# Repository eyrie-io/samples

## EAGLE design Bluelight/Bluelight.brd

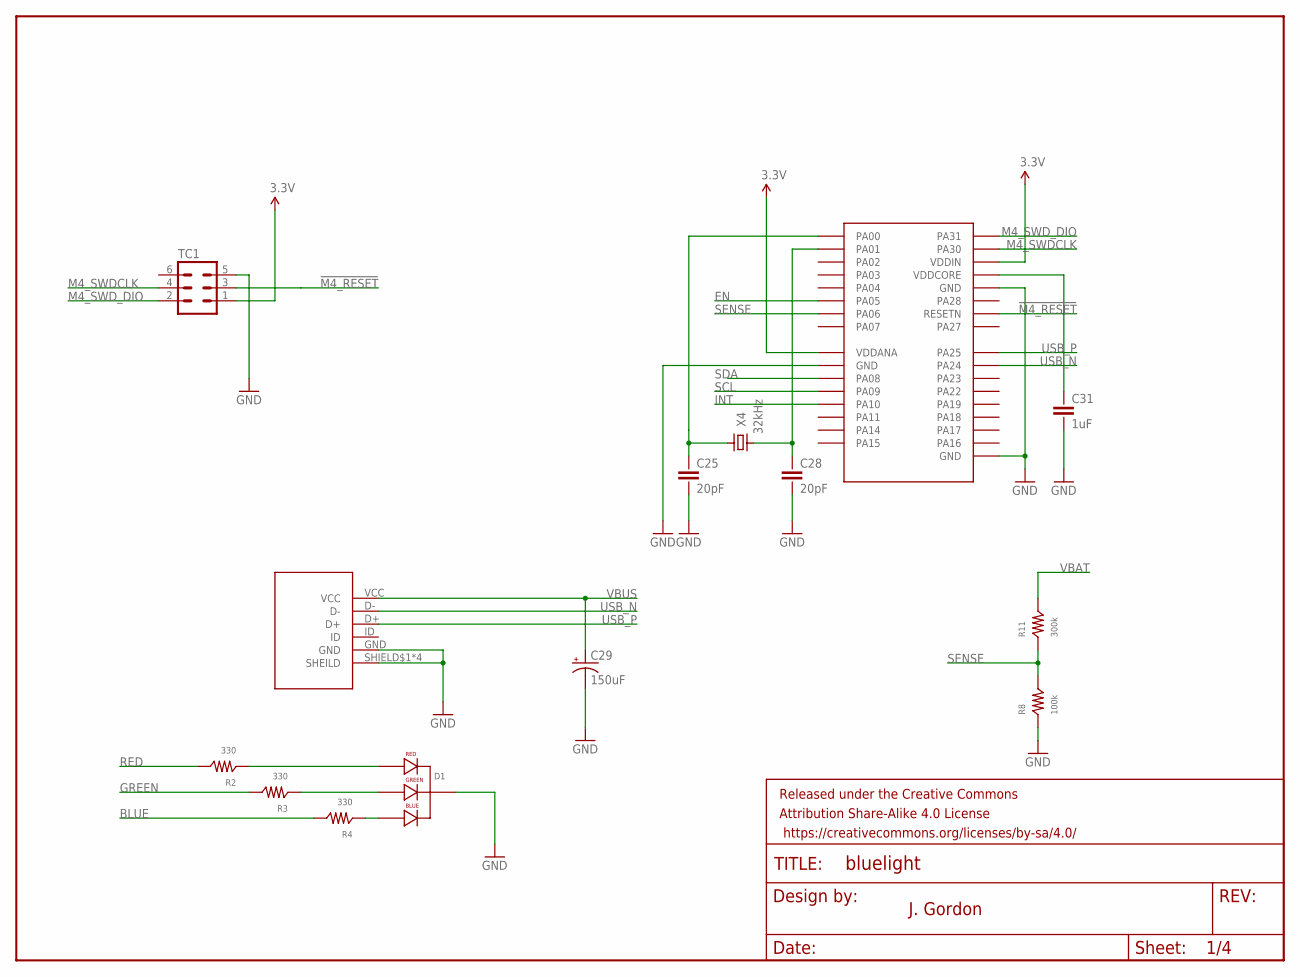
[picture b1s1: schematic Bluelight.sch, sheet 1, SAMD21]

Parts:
C25, C28: 20pF; CAP-0402
C29: 150uF; PANASONIC_C
C31: 1uF; CAP-0402
D1: LED-RGB-CC-THRUDIFFUSE; LED-RGB-THRU
FRAME3: FRAME-LETTERNO_PACKAGE; DUMMY
J5: 10118193-0001LF
R2, R3, R4: 330; RES-0402
R8: 100k; RES-0402
R11: 300k; RES-0402
TC1: TC2030-IDC-NL
U2: ATSAMD21E18A-MUT; QFN32
X4: 32kHz; CRYSTAL-3215

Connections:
3.3V: TC1.1, U2.9 (VDDANA), U2.30 (VDDIN); also elsewhere on the board
!M4_RESET: TC1.3, U2.26 (RESETN); also elsewhere on the board
BLUE: R4.2; also elsewhere on the board
EN: U2.6 (PA05); also elsewhere on the board
GND: C25.1 (2), C28.1 (2), C29.-, C31.1 (2), D1.2 (CATHODE), J5.GND, J5.SHIELD$1 (SHEILD), J5.SHIELD$2 (SHEILD), J5.SHIELD$3 (SHEILD), J5.SHIELD$4 (SHEILD), R8.1, TC1.5, U2.10 (GND), U2.28 (GND), U2.GND; also elsewhere on the board
GREEN: R3.2; also elsewhere on the board
INT: U2.13 (PA10); also elsewhere on the board
M4_SWDCLK: TC1.4, U2.31 (PA30)
M4_SWD_DIO: TC1.2, U2.32 (PA31)
unnamed: D1.4 (BLUE_CATHODE), R4.1
unnamed: D1.3 (GREEN_CATHODE), R3.1
unnamed: C28.2 (1), U2.2 (PA01), X4.P$1 (1)
unnamed: D1.1 (RED_CATHODE), R2.1
unnamed: C25.2 (1), U2.1 (PA00), X4.P$2 (3)
unnamed: C31.2 (1), U2.29 (VDDCORE)
RED: R2.2; also elsewhere on the board
SCL: U2.12 (PA09); also elsewhere on the board
SDA: U2.11 (PA08); also elsewhere on the board
SENSE: R8.2, R11.1, U2.7 (PA06)
USB_N: J5.D-, U2.23 (PA24)
USB_P: J5.D+, U2.24 (PA25)
VBAT: R11.2; also elsewhere on the board
VBUS: C29.+, J5.VCC; also elsewhere on the board

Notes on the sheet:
J. Gordon

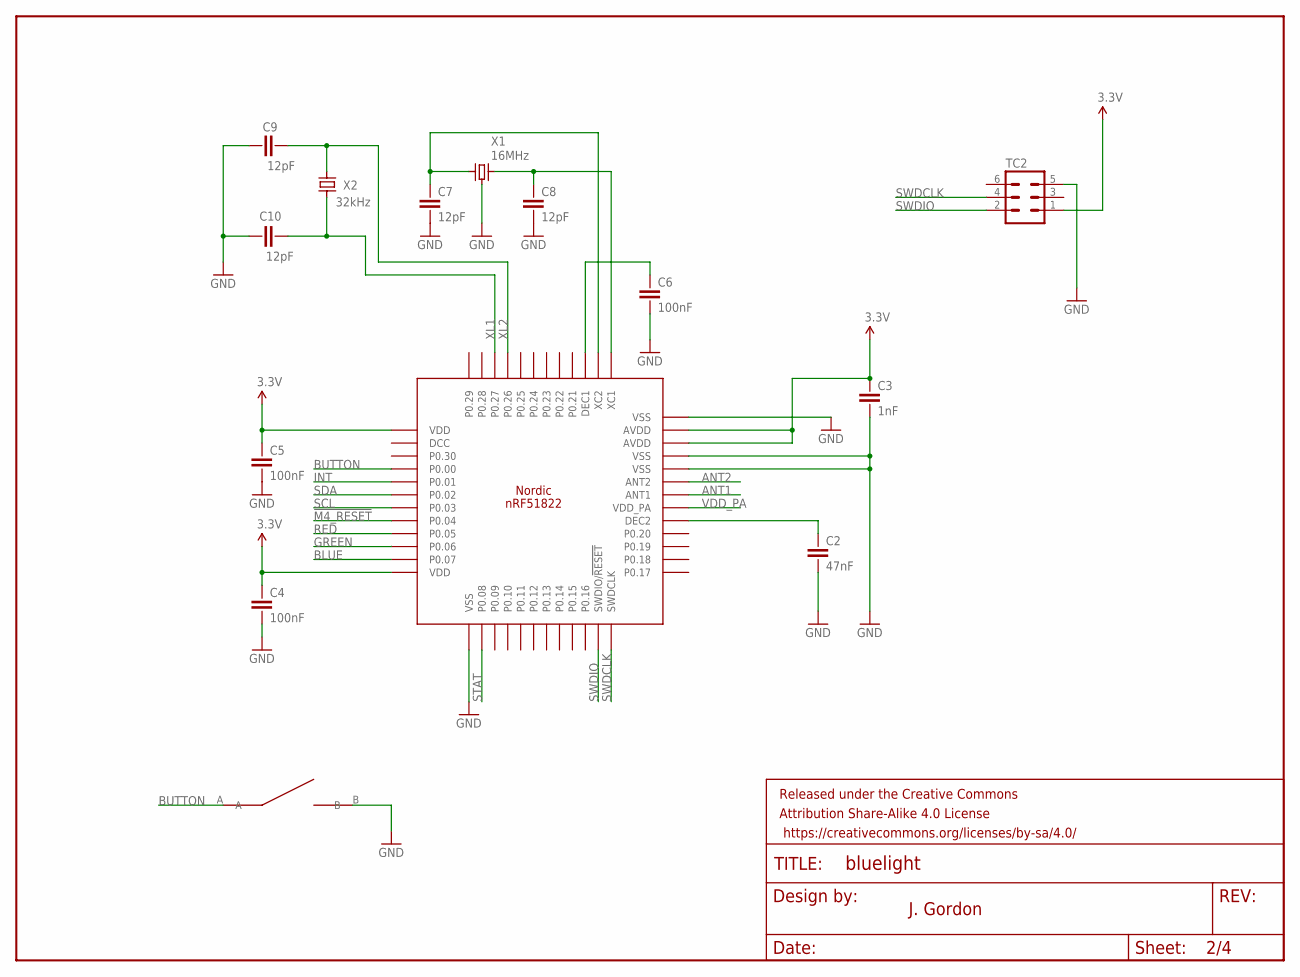
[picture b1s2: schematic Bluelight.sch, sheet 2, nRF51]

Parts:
C2: 47nF; CAP-0402
C3: 1nF; CAP-0402
C4, C5, C6: 100nF; CAP-0402
C7, C8, C9, C10: 12pF; CAP-0402
FRAME1: FRAME-LETTERNO_PACKAGE; DUMMY
TC2: TC2030-IDC-NL
U1: NRF51822
U$1: EVQ-PF206K
X1: 16MHz; CRYSTAL-2520
X2: 32kHz; CRYSTAL-3215

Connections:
3.3V: C3.2 (1), C4.2 (1), C5.2 (1), TC2.1, U1.AVDD@1 (AVDD), U1.AVDD@2 (AVDD), U1.VDD@1 (VDD), U1.VDD@2 (VDD); also elsewhere on the board
!M4_RESET: U1.P0.04; also elsewhere on the board
ANT1: U1.ANT1; also elsewhere on the board
ANT2: U1.ANT2; also elsewhere on the board
BLUE: U1.P0.07; also elsewhere on the board
BUTTON: U1.P0.00, U$1.A
GND: C2.1 (2), C3.1 (2), C4.1 (2), C5.1 (2), C6.1 (2), C7.1 (2), C8.1 (2), C9.2 (1), C10.2 (1), TC2.5, U1.VSS@1 (VSS), U1.VSS@2 (VSS), U1.VSS@3 (VSS), U1.VSS@4 (VSS), U$1.B, X1.GND@1 (GND), X1.GND@2 (GND); also elsewhere on the board
GREEN: U1.P0.06; also elsewhere on the board
INT: U1.P0.01; also elsewhere on the board
unnamed: C2.2 (1), U1.DEC2
unnamed: C6.2 (1), U1.DEC1
unnamed: C8.2 (1), U1.XC1, X1.3
unnamed: C7.2 (1), U1.XC2, X1.1
RED: U1.P0.05; also elsewhere on the board
SCL: U1.P0.03; also elsewhere on the board
SDA: U1.P0.02; also elsewhere on the board
STAT: U1.P0.08; also elsewhere on the board
SWDCLK: TC2.4, U1.SWDCLK
SWDIO: TC2.2, U1.SWDIO/!RESET
VDD_PA: U1.VDD_PA; also elsewhere on the board
XL1: C10.1 (2), U1.P0.27, X2.P$1 (1)
XL2: C9.1 (2), U1.P0.26, X2.P$2 (3)

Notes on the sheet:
J. Gordon

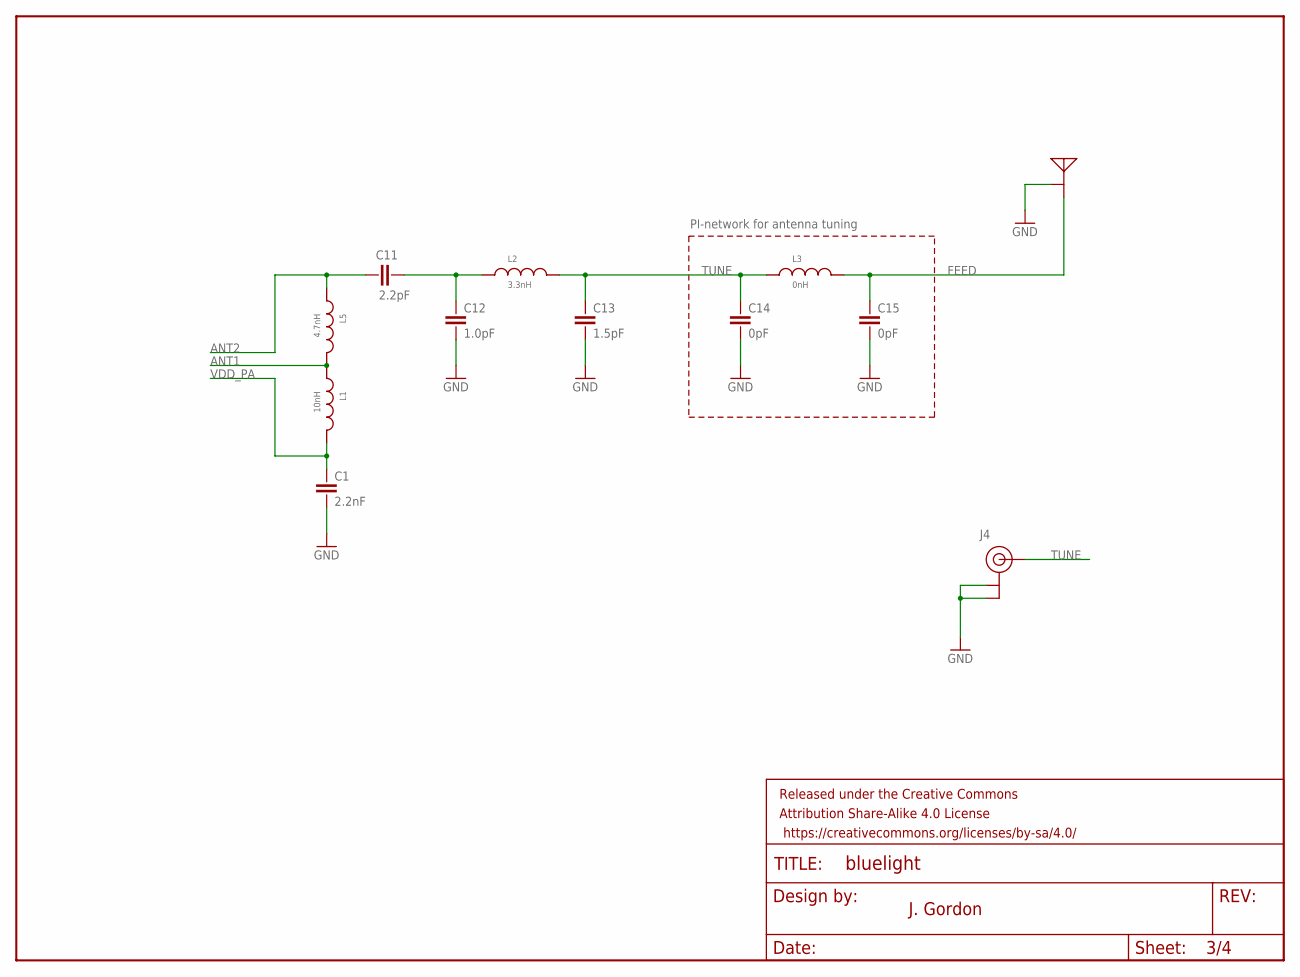
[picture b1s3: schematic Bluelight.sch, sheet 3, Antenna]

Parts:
ANT1: MEANDER-ANT
C1: 2.2nF; CAP-0402
C11: 2.2pF; CAP-0402
C12: 1.0pF; CAP-0402
C13: 1.5pF; CAP-0402
C14, C15: 0pF; CAP-0402
FRAME2: FRAME-LETTERNO_PACKAGE; DUMMY
J4: U.FL
L1: 10nH; IND-0402
L2: 3.3nH; IND-0402
L3: 0nH; IND-0402
L5: 4.7nH; IND-0402

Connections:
ANT1: L1.1, L5.2; also elsewhere on the board
ANT2: C11.2 (1), L5.1; also elsewhere on the board
FEED: ANT1.FEED, C15.2 (1), L3.2
GND: ANT1.GND, C1.1 (2), C12.1 (2), C13.1 (2), C14.1 (2), C15.1 (2), J4.P$1 (GND), J4.P$2 (GND); also elsewhere on the board
unnamed: C11.1 (2), C12.2 (1), L2.1
TUNE: C13.2 (1), C14.2 (1), J4.P$3 (SIGNAL), L2.2, L3.1
VDD_PA: C1.2 (1), L1.2; also elsewhere on the board

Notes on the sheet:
PI-network for antenna tuning
J. Gordon

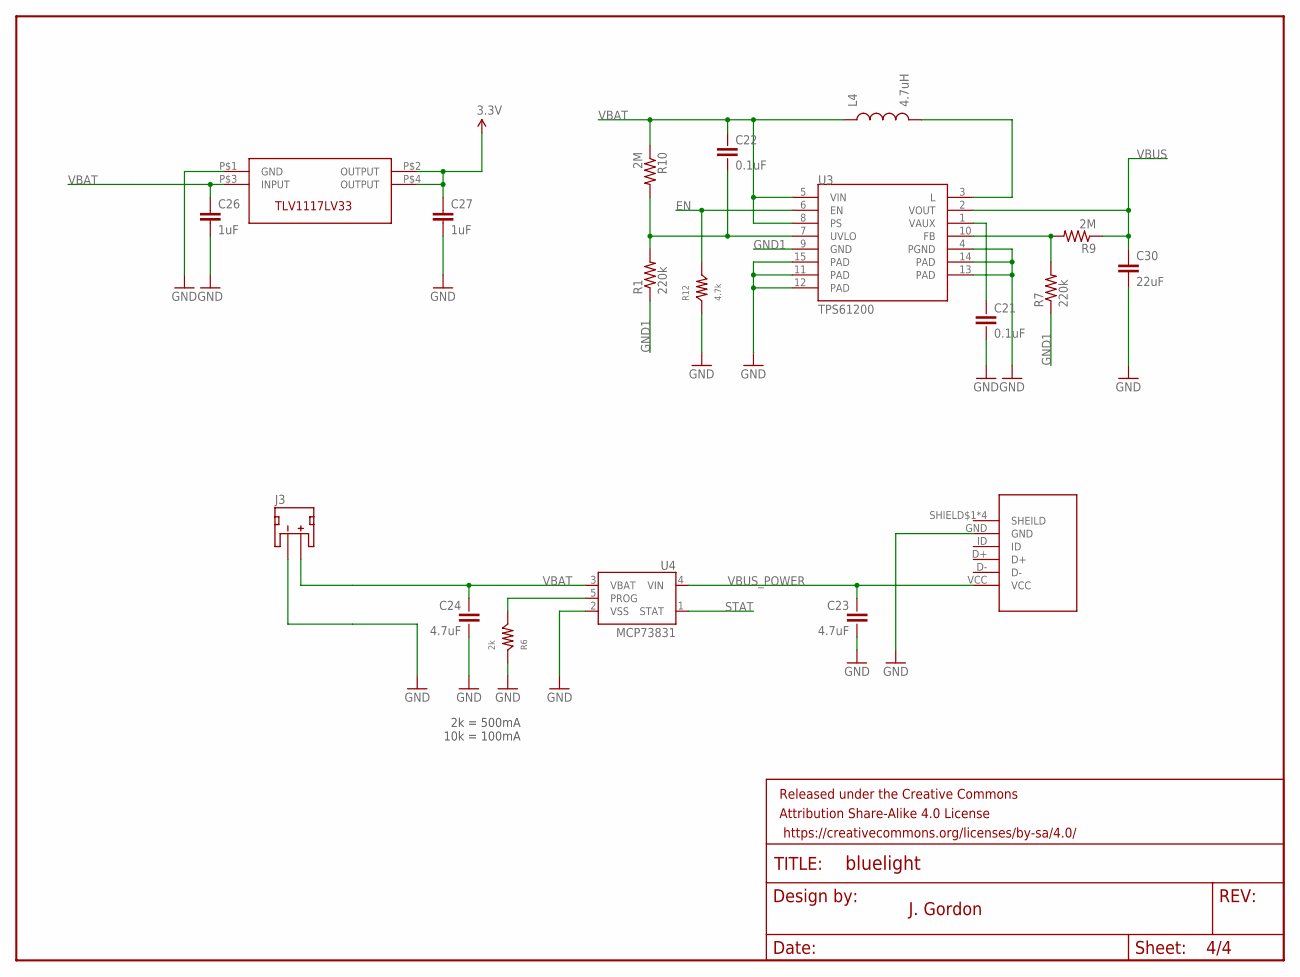
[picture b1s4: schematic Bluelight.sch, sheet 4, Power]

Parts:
C21, C22: 0.1uF; CAP-0402
C23, C24: 4.7uF; CAP-0402
C26, C27: 1uF; 0805
C30: 22uF; 1206
FRAME4: FRAME-LETTERNO_PACKAGE; DUMMY
J1: 10118193-0001LF
J3: JST-2; JST-2-SMD
L4: 4.7uH; CDRH2D09
R1, R7: 220k; 0805
R6: 2k; RES-0402
R9, R10: 2M; 0805
R12: 4.7k; RES-0402
U3: TPS61200; QFN-10_PAD
U4: MCP73831; SOT23-5
U5: TLV1117LV33

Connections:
3.3V: C27.1, U5.P$2 (OUTPUT), U5.P$4 (OUTPUT); also elsewhere on the board
EN: R12.2, U3.6 (EN); also elsewhere on the board
GND: C21.1 (2), C23.1 (2), C24.1 (2), C26.2, C27.2, C30.2, J1.GND, J3.1 (-), R6.1, R12.1, U3.4 (PGND), U3.11 (PAD), U3.12 (PAD), U3.13 (PAD), U3.14 (PAD), U3.15 (PAD), U4.2 (VSS), U5.P$1 (GND); also elsewhere on the board
GND1: R1.1, R7.1, U3.9 (GND)
unnamed: L4.P$2 (2), U3.3 (L)
unnamed: C21.2 (1), U3.1 (VAUX)
unnamed: R7.2, R9.2, U3.10 (FB)
unnamed: C22.1 (2), R1.2, R10.2, U3.7 (UVLO)
PROG: R6.2, U4.5 (PROG)
STAT: U4.1 (STAT); also elsewhere on the board
VBAT: C22.2 (1), C24.2 (1), C26.1, J3.2 (+), L4.P$1 (1), R10.1, U3.5 (VIN), U3.8 (PS), U4.3 (VBAT), U5.P$3 (INPUT); also elsewhere on the board
VBUS: C30.1, R9.1, U3.2 (VOUT); also elsewhere on the board
VBUS_POWER: C23.2 (1), J1.VCC, U4.4 (VIN)

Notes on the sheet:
2k = 500mA 10k = 100mA
J. Gordon

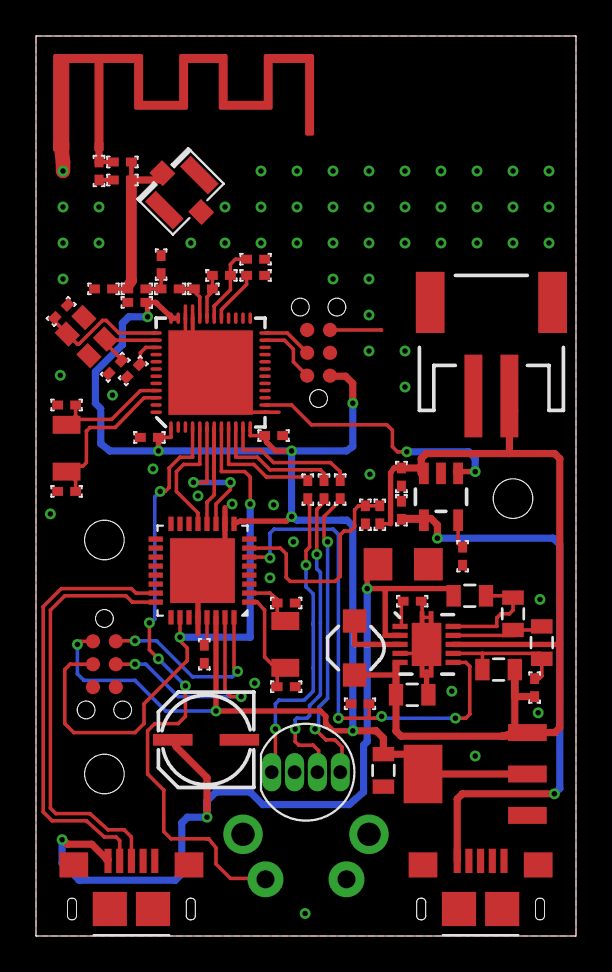
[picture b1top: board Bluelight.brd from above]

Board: 2 copper layers, 30.0 x 50.0 mm, 63 parts (0 on the bottom side), 46 nets.

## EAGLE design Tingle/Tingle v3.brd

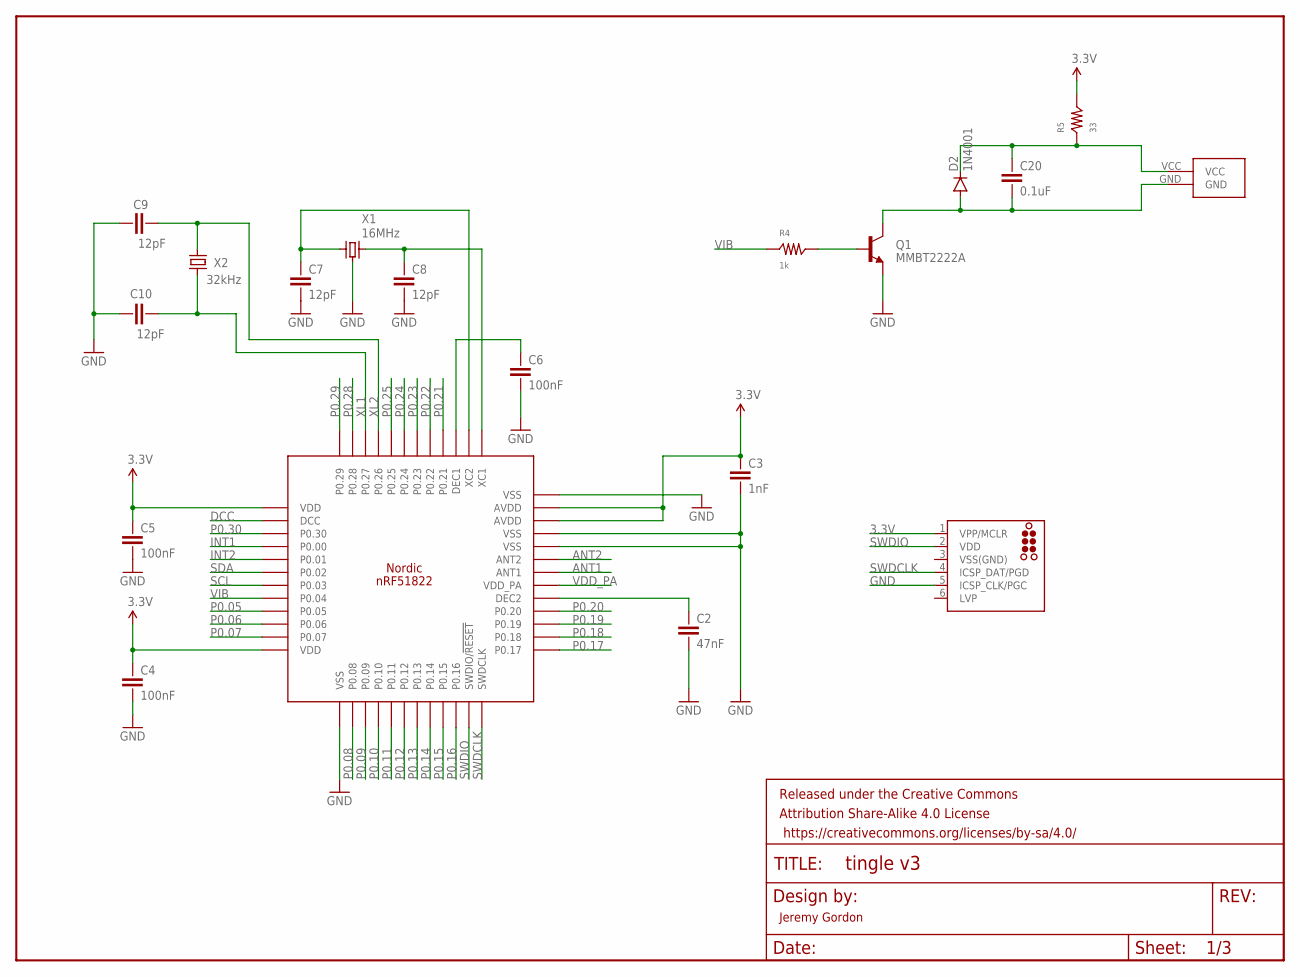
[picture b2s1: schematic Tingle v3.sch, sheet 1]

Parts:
C2: 47nF; CAP-402
C3: 1nF; CAP-402
C4, C5, C6: 100nF; CAP-402
C7, C8, C9, C10: 12pF; CAP-402
C20: 0.1uF; CAP-402
D2: 1N4001; SOD-323
FRAME1: FRAME-LETTER; CREATIVE_COMMONS
J2: TC2030-MCP-NL
Q1: MMBT2222A; SOT23-3
R4: 1k; RES-402
R5: 33; RES-402
U1: NRF51822
U$1: CONN
X1: 16MHz; CRYSTAL-2520
X2: 32kHz; CRYSTAL-3215

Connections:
3.3V: C3.2 (1), C4.2 (1), C5.2 (1), J2.1 (VPP/MCLR), R5.2, U1.AVDD@1 (AVDD), U1.AVDD@2 (AVDD), U1.VDD@1 (VDD), U1.VDD@2 (VDD); also elsewhere on the board
ANT1: U1.ANT1; also elsewhere on the board
ANT2: U1.ANT2; also elsewhere on the board
DCC: U1.DCC
GND: C2.1 (2), C3.1 (2), C4.1 (2), C5.1 (2), C6.1 (2), C7.1 (2), C8.1 (2), C9.2 (1), C10.2 (1), J2.5 (ICSP_CLK/PGC), Q1.2 (E), U1.VSS@1 (VSS), U1.VSS@2 (VSS), U1.VSS@3 (VSS), U1.VSS@4 (VSS), X1.GND@1 (GND), X1.GND@2 (GND); also elsewhere on the board
INT1: U1.P0.00; also elsewhere on the board
INT2: U1.P0.01; also elsewhere on the board
unnamed: C2.2 (1), U1.DEC2
unnamed: C6.2 (1), U1.DEC1
unnamed: C8.2 (1), U1.XC1, X1.3
unnamed: C7.2 (1), U1.XC2, X1.1
unnamed: Q1.1 (B), R4.2
unnamed: C20.2 (1), D2.C, R5.1, U$1.VCC
unnamed: C20.1 (2), D2.A, Q1.3 (C), U$1.GND
P0.05: U1.P0.05
P0.06: U1.P0.06
P0.07: U1.P0.07
P0.08: U1.P0.08
P0.09: U1.P0.09
P0.10: U1.P0.10
P0.11: U1.P0.11
P0.12: U1.P0.12
P0.13: U1.P0.13
P0.14: U1.P0.14
P0.15: U1.P0.15
P0.16: U1.P0.16
P0.17: U1.P0.17
P0.18: U1.P0.18
P0.19: U1.P0.19
P0.20: U1.P0.20
P0.21: U1.P0.21
P0.22: U1.P0.22
P0.23: U1.P0.23
P0.24: U1.P0.24
P0.25: U1.P0.25
P0.28: U1.P0.28
P0.29: U1.P0.29
P0.30: U1.P0.30
SCL: U1.P0.03; also elsewhere on the board
SDA: U1.P0.02; also elsewhere on the board
SWDCLK: J2.4 (ICSP_DAT/PGD), U1.SWDCLK
SWDIO: J2.2 (VDD), U1.SWDIO/!RESET
VDD_PA: U1.VDD_PA; also elsewhere on the board
VIB: R4.1, U1.P0.04
VSS(GND): J2.3 (VSS(GND))
XL1: C10.1 (2), U1.P0.27, X2.P$1 (1)
XL2: C9.1 (2), U1.P0.26, X2.P$2 (3)

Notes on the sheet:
Jeremy Gordon

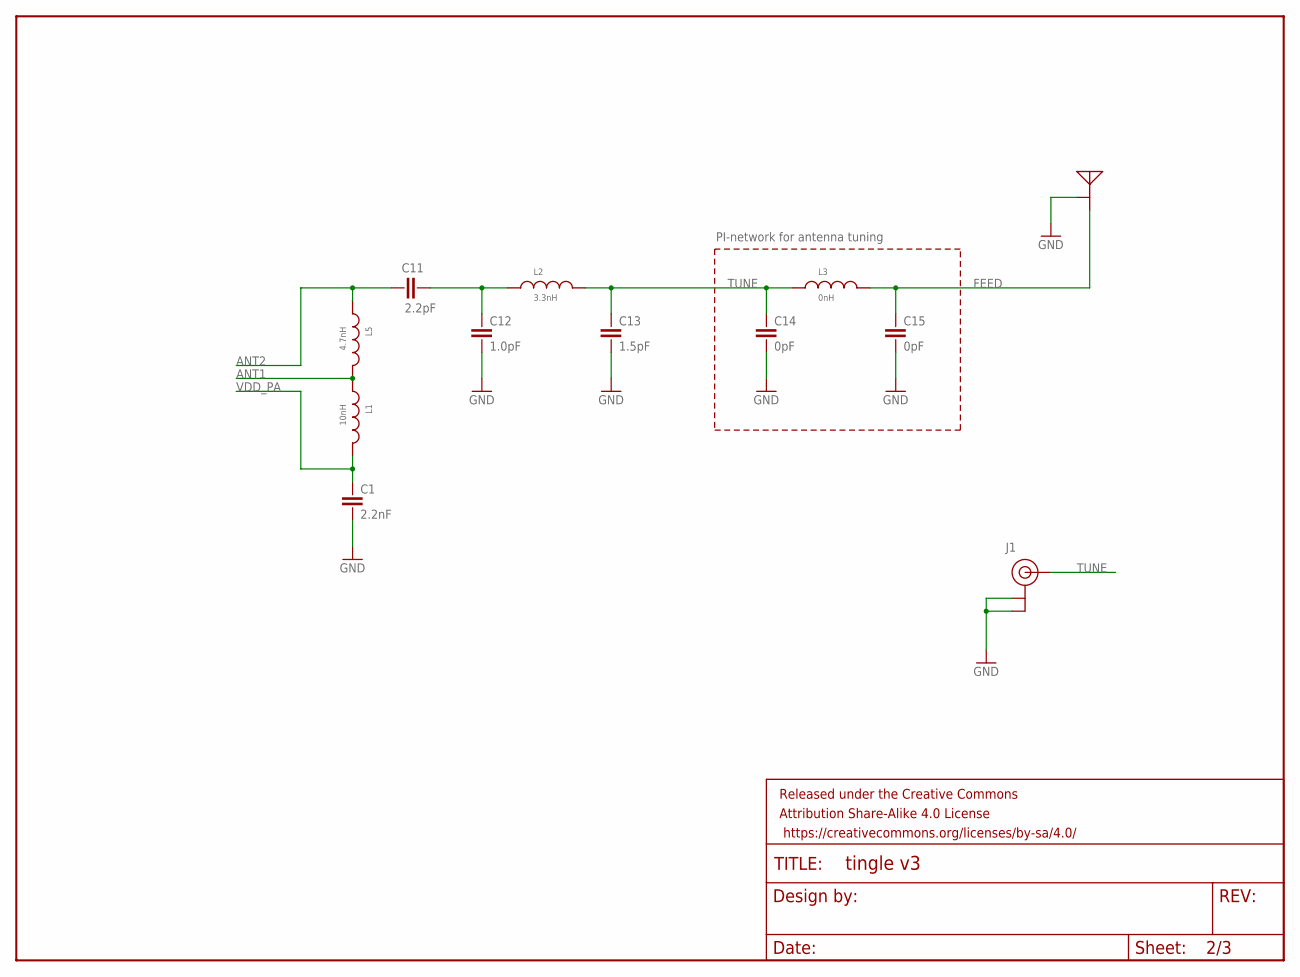
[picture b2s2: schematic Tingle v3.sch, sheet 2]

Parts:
C1: 2.2nF; CAP-402
C11: 2.2pF; CAP-402
C12: 1.0pF; CAP-402
C13: 1.5pF; CAP-402
C14, C15: 0pF; CAP-402
FRAME3: FRAME-LETTER; CREATIVE_COMMONS
J1: U.FL
L1: 10nH; IND-402
L2: 3.3nH; IND-402
L3: 0nH; IND-402
L5: 4.7nH; IND-402
U$2: MEANDER-ANT

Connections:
ANT1: L1.1, L5.2; also elsewhere on the board
ANT2: C11.2 (1), L5.1; also elsewhere on the board
FEED: C15.2 (1), L3.2, U$2.FEED
GND: C1.1 (2), C12.1 (2), C13.1 (2), C14.1 (2), C15.1 (2), J1.P$1 (GND), J1.P$2 (GND), U$2.GND; also elsewhere on the board
unnamed: C11.1 (2), C12.2 (1), L2.1
TUNE: C13.2 (1), C14.2 (1), J1.P$3 (SIGNAL), L2.2, L3.1
VDD_PA: C1.2 (1), L1.2; also elsewhere on the board

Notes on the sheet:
PI-network for antenna tuning

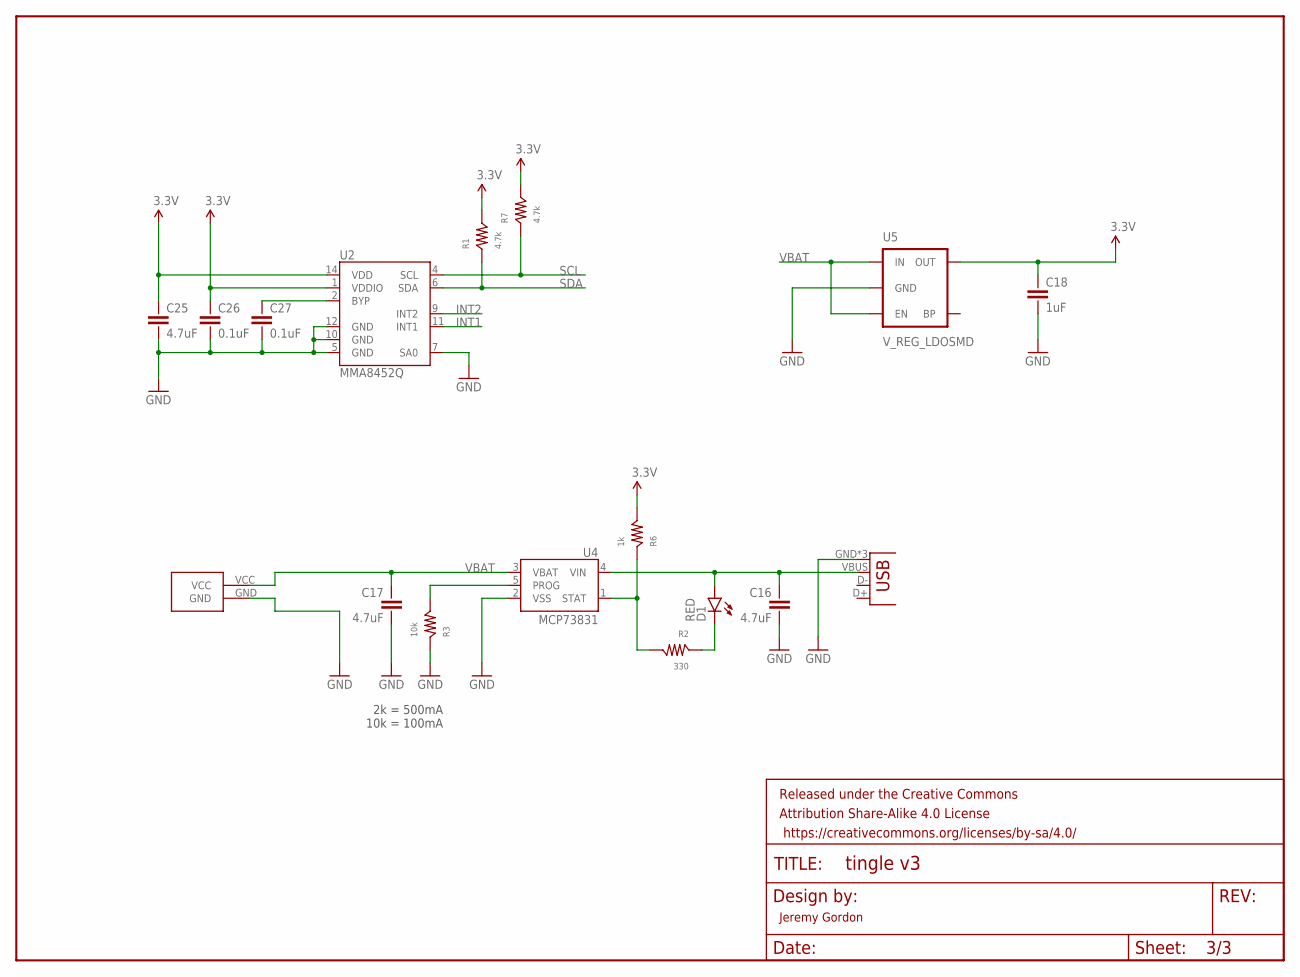
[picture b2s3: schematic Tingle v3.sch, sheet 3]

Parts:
C16, C17, C25: 4.7uF; CAP-402
C18: 1uF; CAP-402
C26, C27: 0.1uF; CAP-402
D1: RED; LED-0603
FRAME2: FRAME-LETTER; CREATIVE_COMMONS
JP2: USB-MICROB
R1, R7: 4.7k; RES-402
R2: 330; RES-402
R3: 10k; RES-402
R6: 1k; RES-402
U2: MMA8452Q; QFN-16_0.5MM
U4: MCP73831; SOT23-5
U5: V_REG_LDOSMD; SOT23-5
U$3: CONN

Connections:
3.3V: C18.2 (1), C25.2 (1), C26.2 (1), R1.2, R6.2, R7.2, U2.1 (VDDIO), U2.14 (VDD), U5.5 (OUT); also elsewhere on the board
GND: C16.1 (2), C17.1 (2), C18.1 (2), C25.1 (2), C26.1 (2), C27.1 (2), JP2.GND, JP2.MT1 (GND), JP2.MT2 (GND), R3.1, U2.5 (GND), U2.7 (SA0), U2.10 (GND), U2.12 (GND), U4.2 (VSS), U5.2 (GND), U$3.GND; also elsewhere on the board
INT1: U2.11 (INT1); also elsewhere on the board
INT2: U2.9 (INT2); also elsewhere on the board
unnamed: C27.2 (1), U2.2 (BYP)
unnamed: D1.C, R2.1
PROG: R3.2, U4.5 (PROG)
SCL: R7.1, U2.4 (SCL); also elsewhere on the board
SDA: R1.1, U2.6 (SDA); also elsewhere on the board
STAT: R2.2, R6.1, U4.1 (STAT)
VBAT: C17.2 (1), U4.3 (VBAT), U5.1 (IN), U5.3 (EN), U$3.VCC
VBUS: C16.2 (1), D1.A, JP2.VBUS, U4.4 (VIN)

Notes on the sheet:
Jeremy Gordon
2k = 500mA 10k = 100mA

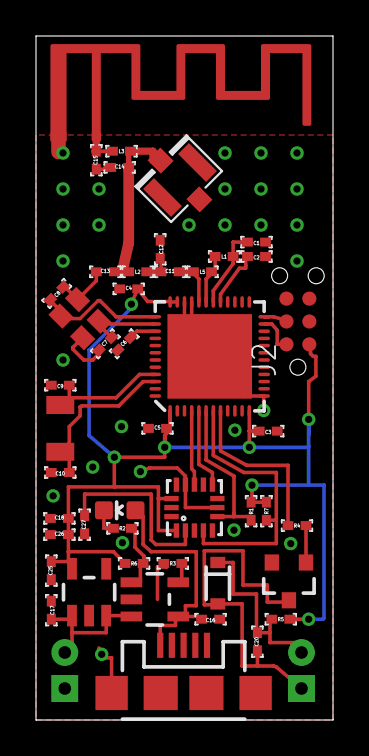
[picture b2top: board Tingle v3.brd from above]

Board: 2 copper layers, 16.5 x 38.0 mm, 51 parts (0 on the bottom side), 30 nets.

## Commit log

2016-09-06 Initial commit.
2016-09-06 Showing holes layer by default on Tingle.
2016-09-12 Fixing up keepout and part numbers.

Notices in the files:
parts and their libraries:
SparkFun-Aesthetics: Licensing: Creative Commons ShareAlike 4.0 International - https://creativecommons.org/licenses/by-sa/4.0
SparkFun-Aesthetics: Released under the Creative Commons Attribution Share-Alike 4.0 License
SparkFun-Aesthetics: https://creativecommons.org/licenses/by-sa/4.0
